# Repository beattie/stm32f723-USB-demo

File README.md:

# STM32F723 USB Passthrough Demo

A hardware and firmware demonstration platform based on the STM32F723VET6, a Cortex-M7
with an embedded USB HS PHY. Inspired by the [Pastilda](https://github.com/nickcoutsos/pastilda)
project, with a goal of providing robust Linux support for USB keyboard passthrough. This project was started as a vehicle to learn Rust and keep my USB up-to date as well as display my limited HW design abilities.

## Concept

The board sits between a USB keyboard and a Linux host. The firmware intercepts keystrokes,
allowing for key remapping, macros, and other HID transformations entirely in hardware —
no kernel modules or userspace daemons required on the host.

## Hardware

Designed in KiCad. The STM32F723 was chosen for its embedded USB HS PHY, which allows
full-speed USB HS without an external PHY chip.

**Key interfaces:**
- USB-C device port to host (USB 2.0 HS)
- USB-A host port for keyboard (USB FS)
- USB-C power input
- MicroSD — for config and macro storage
- SPI LCD connector — optional display
- SWD debug header

**Hardware versions:**
- Rev 0.1 — 2-layer board, initial bring-up (bring-up in progress)
- Rev 0.2 — 4-layer board (F.Cu / GND / 3V3 / B.Cu), revised layout (design in progress)

PCB gerbers for Rev 0.1 are in `kicad/gerbers/`.

## Firmware

Written in Rust using the [Embassy](https://embassy.dev/) async embedded framework.

```
src/main.rs      — application entry point
Cargo.toml       — dependencies
memory.x         — linker memory map for STM32F723VE
```

**Build:**
```bash
cargo build --release
```

Requires the `thumbv7em-none-eabihf` target:
```bash
rustup target add thumbv7em-none-eabihf
```

**Flash:**
```bash
cargo flash --release --chip STM32F723VETx
```
Or use OpenOCD/probe-rs via the SWD header.

## Bill of Materials

See [BOM.md](BOM.md) for the full parts list with Digikey part numbers.

## License

Hardware and firmware are released under CERN-OHL-S v2 / GPL v3 respectively.

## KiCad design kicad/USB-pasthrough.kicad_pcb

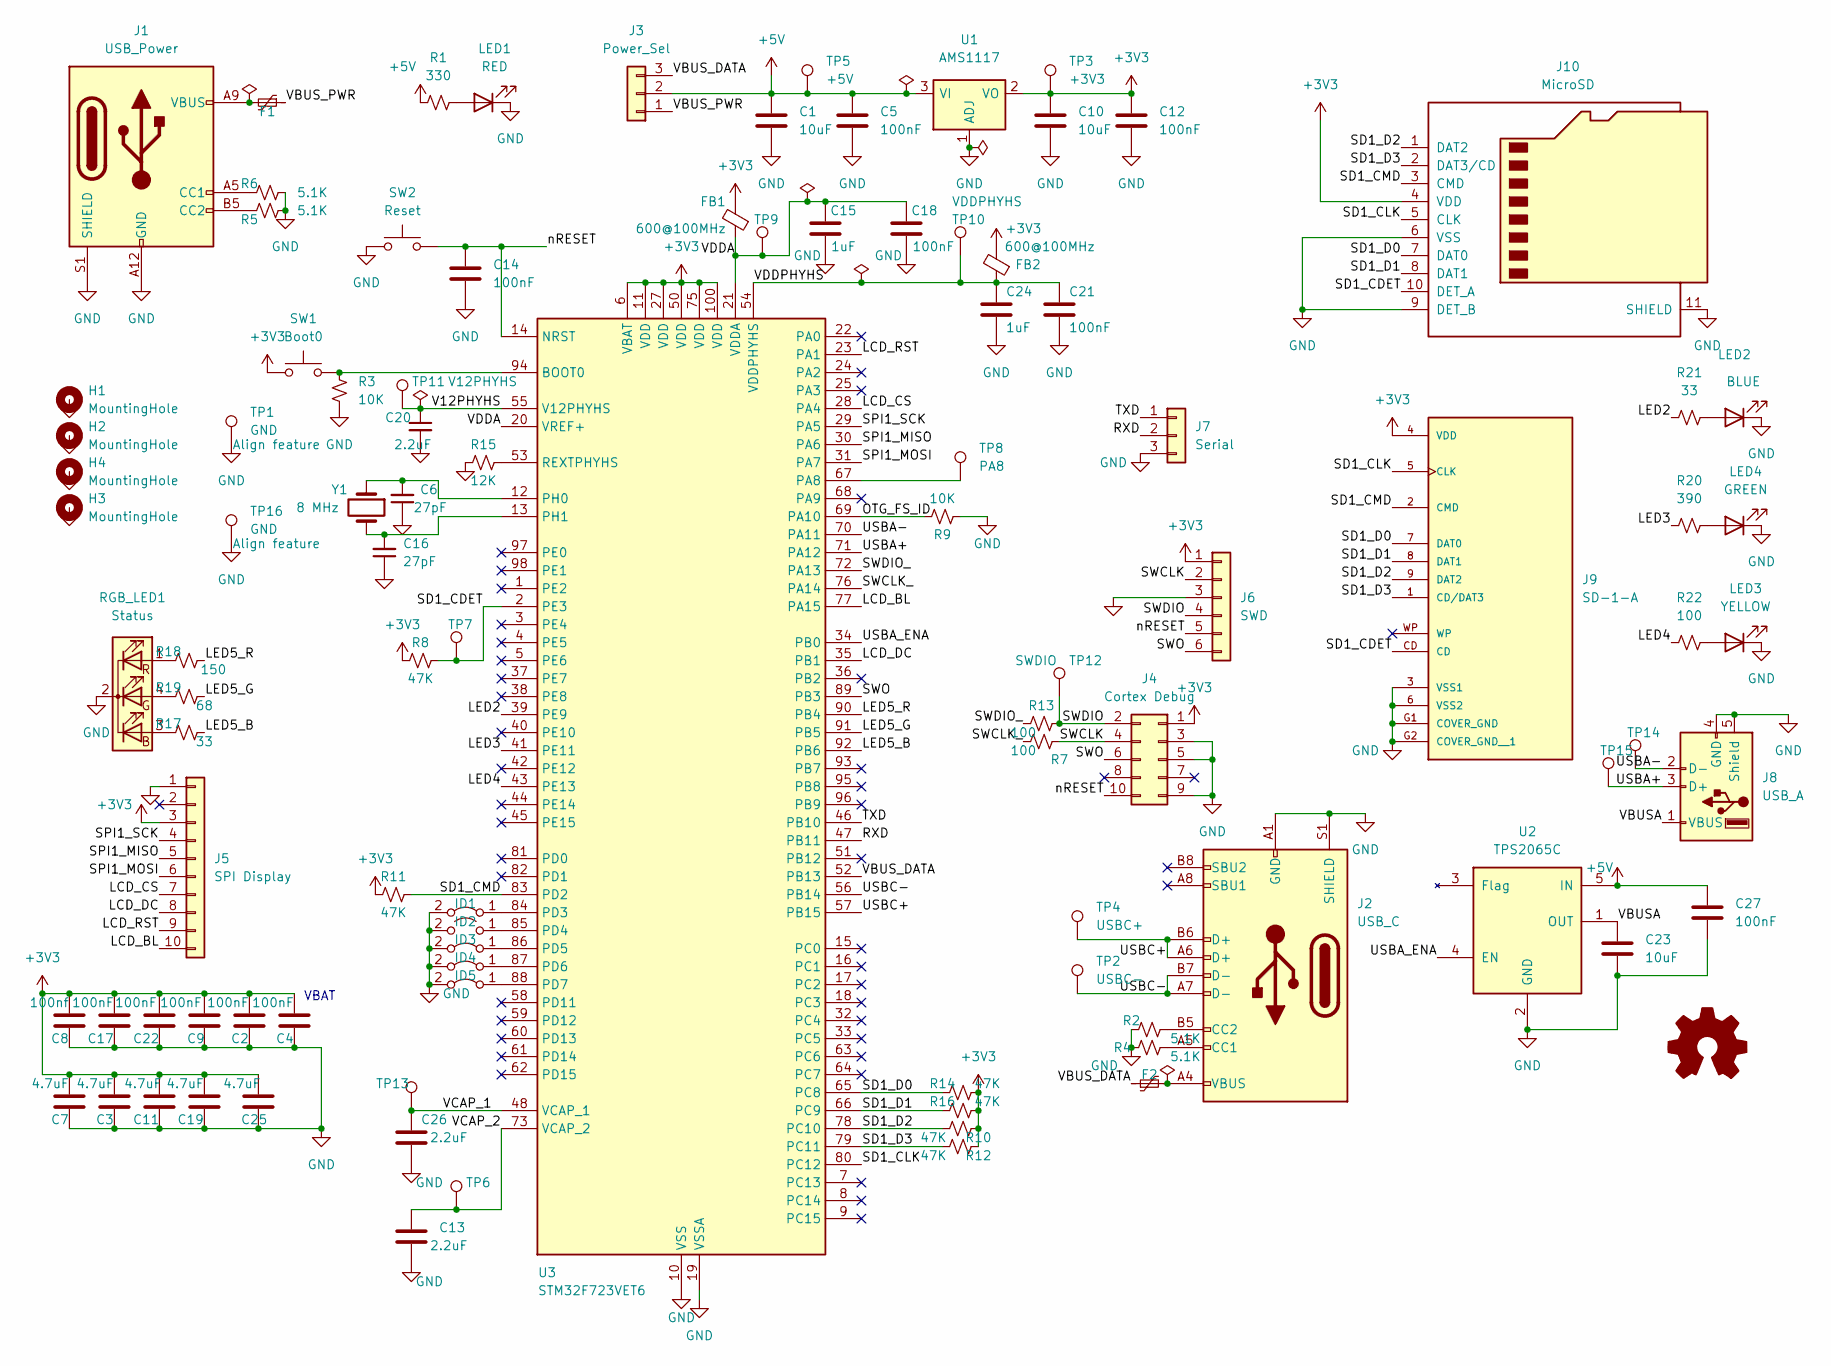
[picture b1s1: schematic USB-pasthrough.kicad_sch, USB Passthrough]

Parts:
C1, C10: 10uF; CP_Radial_D5.0mm_P2.50mm
C2, C4, C5, C9, C12, C14, C17, C18, C21, C22, C27: 100nF; C_0603_1608Metric_Pad1.08x0.95mm_HandSolder
C3, C7, C11, C19, C25: 4.7uF; C_0603_1608Metric_Pad1.08x0.95mm_HandSolder
C6, C16: 27pF; C_0603_1608Metric_Pad1.08x0.95mm_HandSolder
C8: 100nf; C_0603_1608Metric_Pad1.08x0.95mm_HandSolder
C13, C20, C26: 2.2uF; C_0603_1608Metric_Pad1.08x0.95mm_HandSolder
C15, C24: 1uF; C_0603_1608Metric_Pad1.08x0.95mm_HandSolder
C23: 10uF; C_0603_1608Metric_Pad1.08x0.95mm_HandSolder
F1, F2: F; Fuse_1812_4532Metric_Pad1.30x3.40mm_HandSolder
FB1, FB2: 600@100MHz; L_0603_1608Metric_Pad1.05x0.95mm_HandSolder
H1, H2, H3, H4: MountingHole; MountingHole_2.2mm_M2_Pad
ID1, ID3, ID4, ID5: Jumper_2_Bridged; SolderJumper-2_P1.3mm_Bridged_Pad1.0x1.5mm
ID2: Jumper_2_Bridged; SolderJumper-2_P1.3mm_Open_Pad1.0x1.5mm
J1: USB_Power; USB_C_Receptacle_GCT_USB4135-GF-A_6P_TopMnt_Horizontal
J2: USB_C; USB_C_Receptacle_GCT_USB4085
J3: Power_Sel; PinHeader_1x03_P2.54mm_Vertical
J4: Cortex Debug; SAMTEC_SHF-105-01-F-D-TH
J5: SPI Display; PinHeader_1x10_P2.54mm_Vertical
J6: SWD; PinHeader_1x06_P2.54mm_Vertical
J7: Serial; PinHeader_1x03_P2.54mm_Vertical
J8: USB_A; USB_A_Molex_67643_Horizontal
J9: SD-1-A; CUI_SD-1-A; PARTREV 1.0
J10: MicroSD; microSD_HC_Hirose_DM3AT-SF-PEJM5
LED1: RED; LED_0603_1608Metric_Pad1.05x0.95mm_HandSolder
LED2: BLUE; LED_0603_1608Metric_Pad1.05x0.95mm_HandSolder
LED3: YELLOW; LED_0603_1608Metric_Pad1.05x0.95mm_HandSolder
LED4: GREEN; LED_0603_1608Metric_Pad1.05x0.95mm_HandSolder
R1: 330; R_0603_1608Metric_Pad0.98x0.95mm_HandSolder
R2, R4, R5, R6: 5.1K; R_0603_1608Metric_Pad0.98x0.95mm_HandSolder
R3, R9: 10K; R_0603_1608Metric_Pad0.98x0.95mm_HandSolder
R7, R13, R22: 100; R_0603_1608Metric_Pad0.98x0.95mm_HandSolder
R8, R10, R11, R12, R14, R16: 47K; R_0603_1608Metric_Pad0.98x0.95mm_HandSolder
R15: 12K; R_0603_1608Metric_Pad0.98x0.95mm_HandSolder
R17, R21: 33; R_0603_1608Metric_Pad0.98x0.95mm_HandSolder
R18: 150; R_0603_1608Metric_Pad0.98x0.95mm_HandSolder
R19: 68; R_0603_1608Metric_Pad0.98x0.95mm_HandSolder
R20: 390; R_0603_1608Metric_Pad0.98x0.95mm_HandSolder
RGB_LED1: Status; LED_D5.0mm-4_RGB
SW1: Boot0; SW_Push_6mm_2pin_5.08mm
SW2: Reset; SW_Push_6mm_2pin_5.08mm
TP1, TP16: GND; TestPoint_THTPad_D2.0mm_Drill0.8mm_Align
TP2: USBC-; TestPoint_Pad_D1.0mm
TP3: +3V3; TestPoint_Pad_D1.0mm
TP4: USBC+; TestPoint_Pad_D1.0mm
TP5: +5V; TestPoint_Pad_D1.0mm
TP6: VCAP_2; TestPoint_Pad_D1.0mm
TP7: SD1_CDET; TestPoint_Pad_D1.0mm
TP8: PA8; TestPoint_Pad_D1.0mm
TP9: VDDA; TestPoint_Pad_D1.0mm
TP10: VDDPHYHS; TestPoint_Pad_D1.0mm
TP11: V12PHYHS; TestPoint_Pad_D1.0mm
TP12: SWDIO; TestPoint_Pad_D1.0mm
TP13: VCAP_1; TestPoint_Pad_D1.0mm
TP14: USBA-; TestPoint_Pad_D1.0mm
TP15: USBA+; TestPoint_Pad_D1.0mm
U1: AMS1117; SOT-223-3_TabPin2
U2: TPS2065C; SOT-23-5
U3: STM32F723VET6; LQFP-100_14x14mm_P0.5mm
Y1: 8 MHz; Crystal_HC49-U_Vertical

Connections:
+3V3: C2.2, C3.2, C4.2, C7.2, C8.2, C9.1, C10.1, C11.1, C12.1, C17.2, C19.2, C22.1, C25.1, FB1.2, FB2.2, J4.1, J5.3, J6.1, J9.4 (VDD), J10.4 (VDD), R8.1, R10.1, R11.1, R12.1, R14.2, R16.2, SW1.2, TP3.1, U1.2 (VO), U3.6 (VBAT), U3.11 (VDD), U3.27 (VDD), U3.50 (VDD), U3.75 (VDD), U3.100 (VDD)
+5V: C1.1, C5.2, C27.1, J3.2, R1.1, TP5.1, U1.3 (VI), U2.5 (IN)
/LCD_BL: J5.10, U3.77 (PA15)
/LCD_CS: J5.7, U3.28 (PA4)
/LCD_DC: J5.8, U3.35 (PB1)
/LCD_RST: J5.9, U3.23 (PA1)
/LED2: R21.1, U3.39 (PE9)
/LED3: R20.1, U3.41 (PE11)
/LED4: R22.1, U3.43 (PE13)
/LED5_B: R17.2, U3.92 (PB6)
/LED5_G: R19.2, U3.91 (PB5)
/LED5_R: R18.1, U3.90 (PB4)
/OTG_FS_ID: R9.2, U3.69 (PA10)
/RXD: J7.2, U3.25 (PA3), U3.47 (PB11)
/SD1_CDET: J9.CD, J10.10 (DET_A), R8.2, TP7.1, U3.2 (PE3)
/SD1_CLK: J9.5 (CLK), J10.5 (CLK), U3.80 (PC12)
/SD1_CMD: J9.2 (CMD), J10.3 (CMD), R11.2, U3.83 (PD2)
/SD1_D0: J9.7 (DAT0), J10.7 (DAT0), R14.1, U3.65 (PC8)
/SD1_D1: J9.8 (DAT1), J10.8 (DAT1), R16.1, U3.66 (PC9)
/SD1_D2: J9.9 (DAT2), J10.1 (DAT2), R10.2, U3.78 (PC10)
/SD1_D3: J9.1 (CD/DAT3), J10.2 (DAT3/CD), R12.2, U3.79 (PC11)
/SPI1_MISO: J5.5, U3.30 (PA6)
/SPI1_MOSI: J5.6, U3.31 (PA7)
/SPI1_SCK: J5.4, U3.29 (PA5)
/SWCLK: J4.4, J6.2, R7.2
/SWCLK_: R7.1, U3.76 (PA14)
/SWDIO: J4.2, J6.4, R13.2, TP12.1
/SWDIO_: R13.1, U3.72 (PA13)
/SWO: J4.6, J6.6, U3.89 (PB3)
/TXD: J7.1, U3.24 (PA2), U3.46 (PB10)
/USBA+: J8.3 (D+), TP15.1, U3.71 (PA12)
/USBA-: J8.2 (D-), TP14.1, U3.70 (PA11)
/USBA_ENA: U2.4 (EN), U3.34 (PB0)
/USBC+: J2.A6 (D+), J2.B6 (D+), TP4.1, U3.57 (PB15)
/USBC-: J2.A7 (D-), J2.B7 (D-), TP2.1, U3.56 (PB14)
/V12PHYHS: C20.1, TP11.1, U3.55 (V12PHYHS)
/VBUSA: C23.1, J8.1 (VBUS), U2.1 (OUT)
/VBUS_DATA: F2.1, J3.3, U3.52 (PB13)
/VBUS_PWR: F1.1, J3.1
/VCAP_1: C26.1, TP13.1, U3.48 (VCAP_1)
/VCAP_2: C13.1, TP6.1, U3.73 (VCAP_2)
/VDDA: C15.1, C18.1, FB1.1, TP9.1, U3.20 (VREF+), U3.21 (VDDA)
/VDDPHYHS: C21.1, C24.1, FB2.1, TP10.1, U3.54 (VDDPHYHS)
/nRESET: C14.1, J4.10, J6.5, SW2.1, U3.14 (NRST)
GND: C1.2, C2.1, C3.1, C4.1, C5.1, C6.1, C7.1, C8.1, C9.2, C10.2, C11.2, C12.2, C13.2, C14.2, C15.2, C16.1, C17.1, C18.2, C19.1, C20.2, C21.2, C22.2, C23.2, C24.2, C25.2, C26.2, C27.2, ID1.2 (B), ID2.2 (B), ID3.2 (B), ID4.2 (B), ID5.2 (B), J1.A12 (GND), J1.B12 (GND), J1.S1 (SHIELD), J2.A1 (GND), J2.A12 (GND), J2.B1 (GND), J2.B12 (GND), J2.S1 (SHIELD), J4.3, J4.5, J4.9, J5.1, J6.3, J7.3, J8.4 (GND), J8.5 (Shield), J9.3 (VSS1), J9.6 (VSS2), J9.G1 (COVER_GND), J9.G2 (COVER_GND__1), J10.6 (VSS), J10.9 (DET_B), J10.11 (SHIELD), LED1.1 (K), LED2.1 (K), LED3.1 (K), LED4.1 (K), R2.2, R3.2, R4.2, R5.2, R6.2, R9.1, R15.2, RGB_LED1.2 (K), SW2.2, TP1.1, TP16.1, U1.1 (ADJ), U2.2 (GND), U3.10 (VSS), U3.19 (VSSA), U3.26 (VSS), U3.49 (VSS), U3.74 (VSS), U3.99 (VSS)
unnamed: C6.2, U3.12 (PH0), Y1.1
unnamed: C16.2, U3.13 (PH1), Y1.2
unnamed: F1.2, J1.A9 (VBUS), J1.B9 (VBUS)
unnamed: F2.2, J2.A4 (VBUS), J2.A9 (VBUS), J2.B4 (VBUS), J2.B9 (VBUS)
unnamed: ID1.1 (A), U3.84 (PD3)
unnamed: ID2.1 (A), U3.85 (PD4)
unnamed: ID3.1 (A), U3.86 (PD5)
unnamed: ID4.1 (A), U3.87 (PD6)
unnamed: ID5.1 (A), U3.88 (PD7)
unnamed: J1.A5 (CC1), R6.1
unnamed: J1.B5 (CC2), R5.1
unnamed: J2.A5 (CC1), R4.1
unnamed: J2.B5 (CC2), R2.1
unnamed: LED1.2 (A), R1.2
unnamed: LED2.2 (A), R21.2
unnamed: LED4.2 (A), R20.2
unnamed: LED3.2 (A), R22.2
unnamed: R3.1, SW1.1, U3.94 (BOOT0)
unnamed: R15.1, U3.53 (REXTPHYHS)
unnamed: R17.1, RGB_LED1.3 (BA)
unnamed: R18.2, RGB_LED1.1 (RA)
unnamed: R19.1, RGB_LED1.4 (GA)
unnamed: TP8.1, U3.67 (PA8)

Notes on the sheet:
VBAT

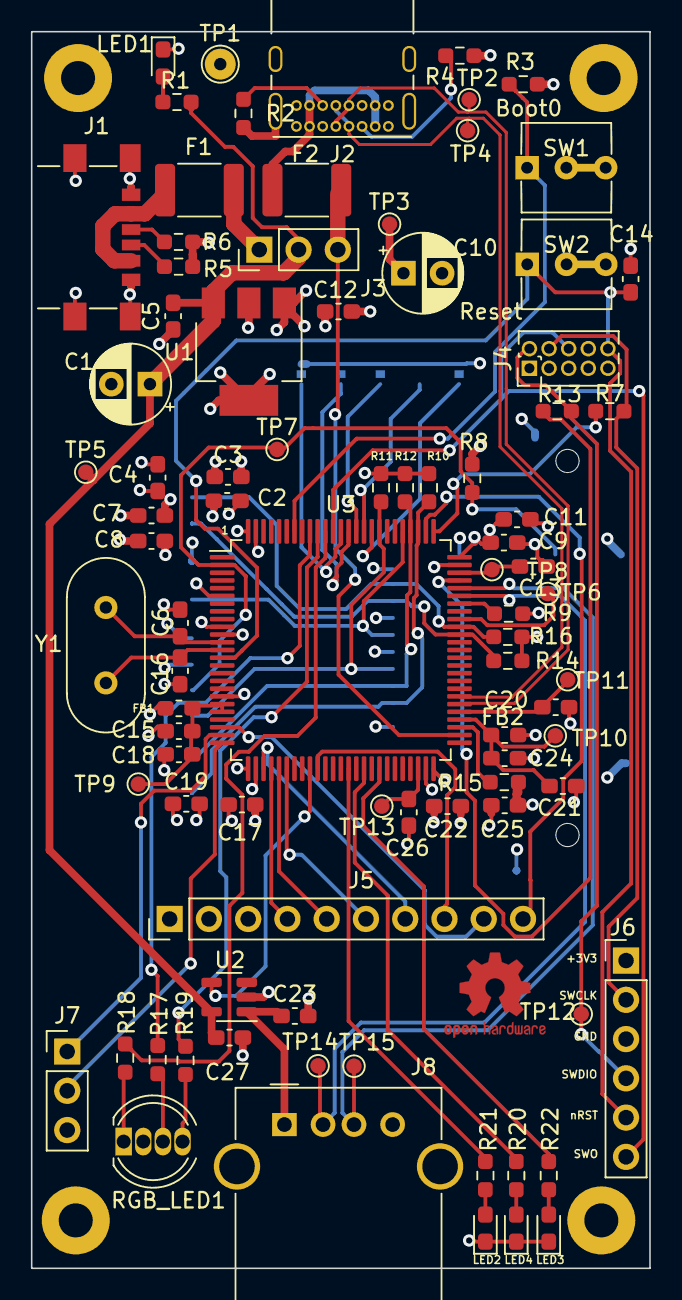
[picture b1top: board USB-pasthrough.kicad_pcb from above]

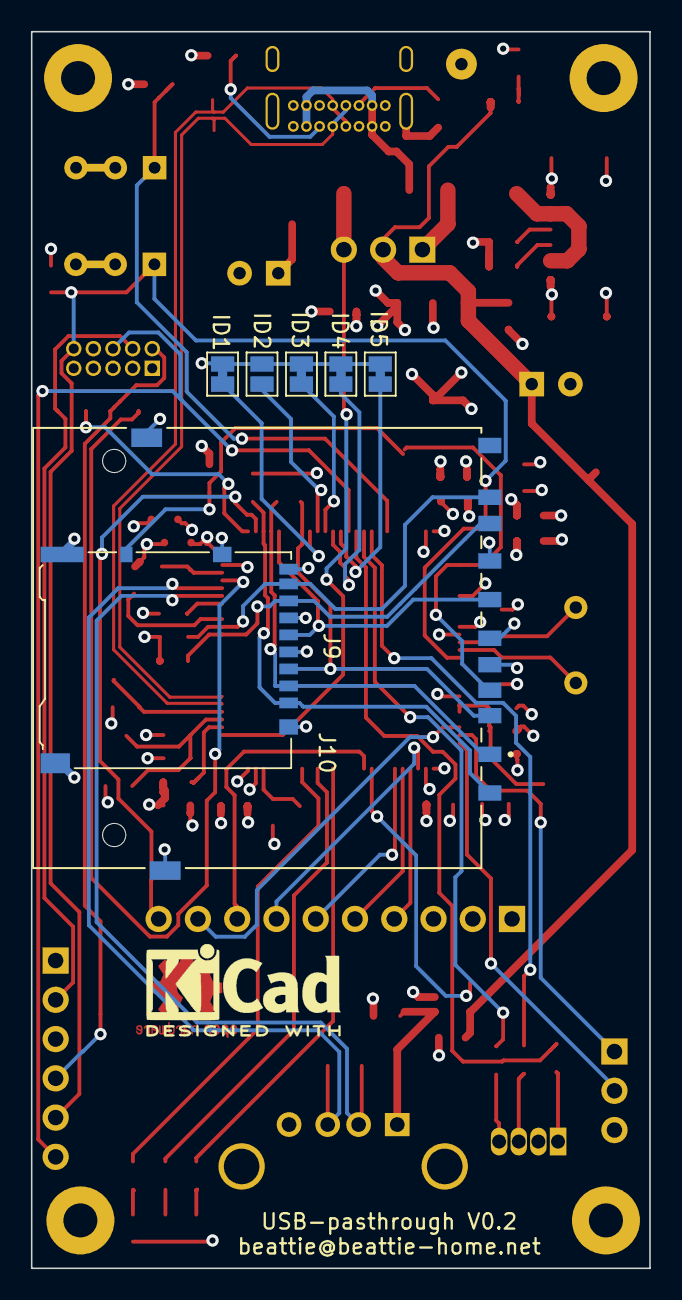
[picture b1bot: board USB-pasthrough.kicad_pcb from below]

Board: 4 copper layers, 40.0 x 80.0 mm, 98 parts (7 on the bottom side), 68 nets.

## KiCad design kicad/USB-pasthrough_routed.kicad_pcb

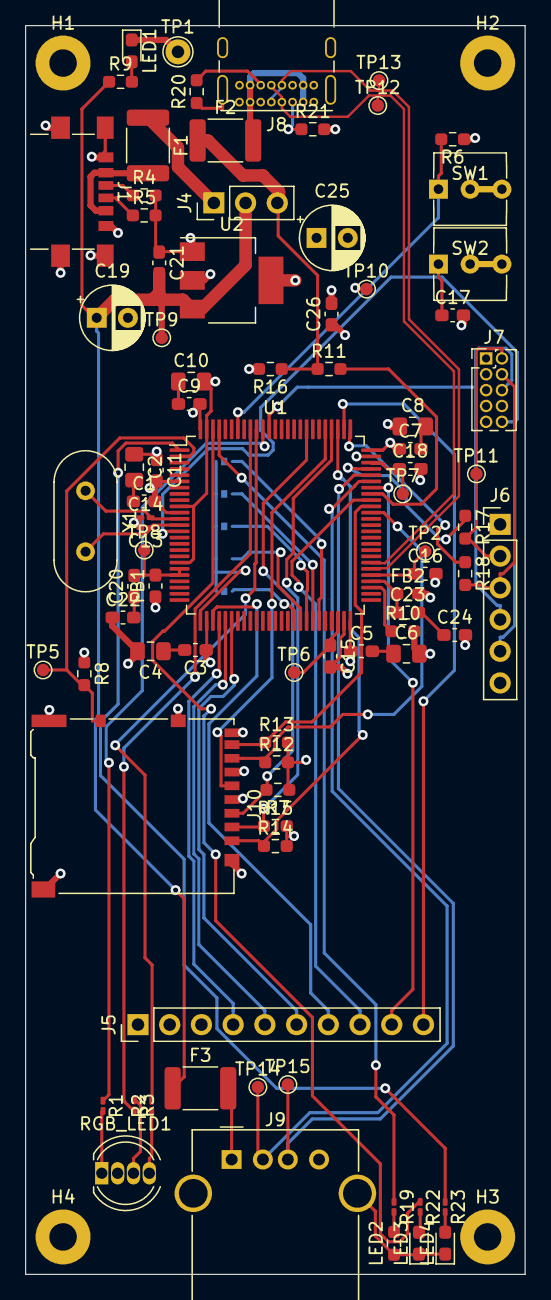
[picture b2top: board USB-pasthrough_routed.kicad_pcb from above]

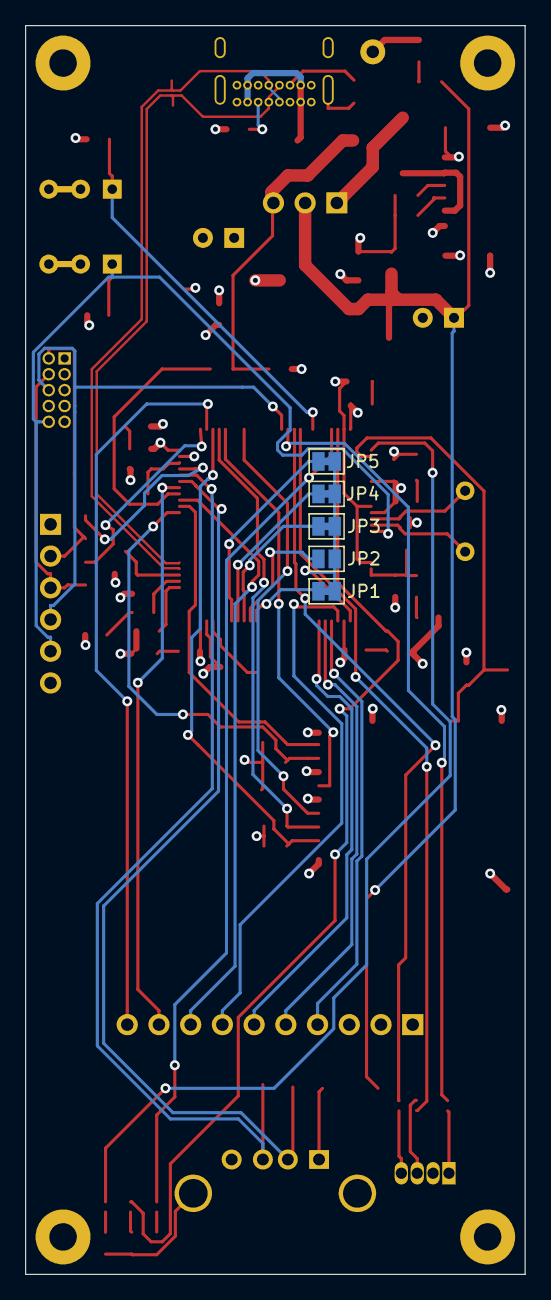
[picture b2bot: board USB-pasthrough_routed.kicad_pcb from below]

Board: 4 copper layers, 40.0 x 100.0 mm, 93 parts (5 on the bottom side), 71 nets.

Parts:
C1: 100nf; C_0603_1608Metric_Pad1.08x0.95mm_HandSolder
C2, C4, C6, C8, C10: 4.7uF; C_0805_2012Metric_Pad1.18x1.45mm_HandSolder
C3, C5, C7, C9, C11, C17, C21, C22, C24, C26: 100nF; C_0603_1608Metric_Pad1.08x0.95mm_HandSolder
C13, C14: 27pF; C_0201_0603Metric_Pad0.64x0.40mm_HandSolder
C15, C16, C18: 2.2uF; C_0603_1608Metric_Pad1.08x0.95mm_HandSolder
C19, C25: 10uF; CP_Radial_D5.0mm_P2.50mm
C20, C23: 1uF; C_0603_1608Metric_Pad1.08x0.95mm_HandSolder
F1, F2, F3: F; Fuse_1812_4532Metric_Pad1.30x3.40mm_HandSolder
FB1, FB2: 600@100MHz; L_0603_1608Metric_Pad1.05x0.95mm_HandSolder
H1, H2, H3, H4: MountingHole; MountingHole_2.2mm_M2_Pad
J1: USB_Power; USB_C_Receptacle_GCT_USB4135-GF-A_6P_TopMnt_Horizontal
J4: Power_Sel; PinHeader_1x03_P2.54mm_Vertical
J5: SPI Display; PinHeader_1x10_P2.54mm_Vertical
J6: SWD; PinHeader_1x06_P2.54mm_Vertical
J7: Cortex Debug; PinHeader_2x05_P1.27mm_Vertical
J8: USB_C; USB_C_Receptacle_GCT_USB4085
J9: USB_A; USB_A_Molex_67643_Horizontal
J10: MicroSD; microSD_HC_Hirose_DM3AT-SF-PEJM5
JP1: ID0; SolderJumper-2_P1.3mm_Bridged_Pad1.0x1.5mm
JP2: ID1; SolderJumper-2_P1.3mm_Open_Pad1.0x1.5mm
JP3: ID2; SolderJumper-2_P1.3mm_Bridged_Pad1.0x1.5mm
JP4: ID3; SolderJumper-2_P1.3mm_Bridged_Pad1.0x1.5mm
JP5: ID4; SolderJumper-2_P1.3mm_Bridged_Pad1.0x1.5mm
LED1: RED; LED_0603_1608Metric_Pad1.05x0.95mm_HandSolder
LED2: BLUE; R_0603_1608Metric_Pad0.98x0.95mm_HandSolder
LED3: GREEN; LED_0603_1608Metric_Pad1.05x0.95mm_HandSolder
LED4: YELLOW; LED_0603_1608Metric_Pad1.05x0.95mm_HandSolder
R1, R23: 150; R_0201_0603Metric_Pad0.64x0.40mm_HandSolder
R2, R22: 68; R_0201_0603Metric_Pad0.64x0.40mm_HandSolder
R3, R19: 33; R_0201_0603Metric_Pad0.64x0.40mm_HandSolder
R4, R5, R20, R21: 5.1K; R_0603_1608Metric_Pad0.98x0.95mm_HandSolder
R6: 10K; R_0603_1608Metric_Pad0.98x0.95mm_HandSolder
R7, R8, R12, R13, R14, R15: 47K; R_0603_1608Metric_Pad0.98x0.95mm_HandSolder
R9: 330; R_0603_1608Metric_Pad0.98x0.95mm_HandSolder
R10: 12K; R_0603_1608Metric_Pad0.98x0.95mm_HandSolder
R11: 100K; R_0603_1608Metric_Pad0.98x0.95mm_HandSolder
R16: 220k; R_0603_1608Metric_Pad0.98x0.95mm_HandSolder
R17, R18: 100; R_0603_1608Metric_Pad0.98x0.95mm_HandSolder
RGB_LED1: Status; LED_D5.0mm-4_RGB
SW1: Boot0; SW_Push_6mm_2pin_5.08mm
SW2: Reset; SW_Push_6mm_2pin_5.08mm
TP1: GND; TestPoint_THTPad_D2.0mm_Drill1.0mm
TP2: V12PHYHS; TestPoint_Pad_D1.0mm
TP5: MMC1_CDET; TestPoint_Pad_D1.0mm
TP6: VCAP_1; TestPoint_Pad_D1.0mm
TP7: VCAP_2; TestPoint_Pad_D1.0mm
TP8: VDDA; TestPoint_Pad_D1.0mm
TP9: +5V; TestPoint_Pad_D1.0mm
TP10: +3V3; TestPoint_Pad_D1.0mm
TP11: SWDIO; TestPoint_Pad_D1.0mm
TP12: USBC+; TestPoint_Pad_D1.0mm
TP13: USBC-; TestPoint_Pad_D1.0mm
TP14: USBA-; TestPoint_Pad_D1.0mm
TP15: USBA+; TestPoint_Pad_D1.0mm
U1: STM32F723VET6; LQFP-100_14x14mm_P0.5mm
U2: AMS1117; SOT-223-3_TabPin2
Y1: 8 MHz; Crystal_HC49-U_Vertical

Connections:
+3V3: C1.2, C3.1, C5.1, C7.1, C9.2, C11.2, C25.1, C26.2, FB1.1, FB2.2, J5.3, J6.1, J7.1, J10.4 (VDD), R7.1, R8.1, R12.2, R13.2, R14.2, R15.2, SW1.2, TP10.1, U1.6 (VBAT), U1.11 (VDD), U1.27 (VDD), U1.50 (VDD), U1.75 (VDD), U1.100 (VDD), U2.2 (VO)
+5V: C19.1, C21.2, F3.1, J4.2, R9.1, TP9.1, U2.3 (VI)
/ID0: JP1.1 (A), U1.41 (PE11)
/ID1: JP2.1 (A), U1.42 (PE12)
/ID2: JP3.1 (A), U1.43 (PE13)
/ID3: JP4.1 (A), U1.44 (PE14)
/ID4: JP5.1 (A), U1.45 (PE15)
/LCD_BL: J5.10, U1.77 (PA15)
/LCD_CS: J5.7, U1.28 (PA4)
/LCD_DC: J5.8, U1.67 (PA8)
/LCD_RST: J5.9, U1.69 (PA10)
/LED2: R19.1, U1.97 (PE0)
/LED3: R22.1, U1.98 (PE1)
/LED4: R23.1, U1.1 (PE2)
/LED5_B: R3.2, U1.92 (PB6)
/LED5_G: R2.2, U1.91 (PB5)
/LED5_R: R1.1, U1.90 (PB4)
/MMC1_CDET: J10.10 (DET_A), R8.2, TP5.1, U1.2 (PE3)
/MMC1_CLK: J10.5 (CLK), U1.80 (PC12)
/MMC1_CMD: J10.3 (CMD), R7.2, U1.83 (PD2)
/MMC1_D0: J10.7 (DAT0), R12.1, U1.65 (PC8)
/MMC1_D1: J10.8 (DAT1), R13.1, U1.66 (PC9)
/MMC1_D2: J10.1 (DAT2), R14.1, U1.78 (PC10)
/MMC1_D3: J10.2 (DAT3/CD), R15.1, U1.79 (PC11)
/PA13: R17.1, U1.72 (PA13)
/PA14: R18.1, U1.76 (PA14)
/SPI1_MISO: J5.5, U1.30 (PA6)
/SPI1_MOSI: J5.6, U1.31 (PA7)
/SPI1_SCK: J5.4, U1.29 (PA5)
/SWCLK: J6.3, J7.4, R18.2
/SWDIO: J6.2, J7.2, R17.2, TP11.1
/SWO: J6.4, J7.6, U1.89 (PB3)
/USBA+: J9.3 (D+), TP15.1, U1.71 (PA12)
/USBA-: J9.2 (D-), TP14.1, U1.70 (PA11)
/USBC+: J8.A6 (D+), J8.B6 (D+), TP12.1, U1.57 (PB15)
/USBC-: J8.A7 (D-), J8.B7 (D-), TP13.1, U1.56 (PB14)
/V12PHYHS: C16.1, TP2.1, U1.55 (V12PHYHS)
/VBUS_DATA: F2.1, J4.3, R11.1, R16.1
/VBUS_PWR: F1.1, J4.1
/VCAP_1: C15.1, TP6.1, U1.48 (VCAP_1)
/VCAP_2: C18.1, TP7.1, U1.73 (VCAP_2)
/VDDA: C20.2, FB1.2, TP8.1, U1.20 (VREF+), U1.21 (VDDA)
/nRESET: C17.1, J6.5, J7.10, SW2.1, U1.14 (NRST)
GND: C2.1, C4.2, C6.2, C8.1, C10.2, C11.1, C13.2, C14.1, C15.2, C16.2, C17.2, C18.2, C19.2, C21.1, C22.1, C24.2, C25.2, C26.1, J1.A12 (GND), J1.B12 (GND), J1.S1 (SHIELD), J5.1, J6.6, J7.3, J7.5, J7.9, J8.A1 (GND), J8.A12 (GND), J8.B1 (GND), J8.B12 (GND), J8.S1 (SHIELD), J9.4 (GND), J9.5 (Shield), J10.6 (VSS), J10.9 (DET_B), J10.11 (SHIELD), JP1.2 (B), JP2.2 (B), JP3.2 (B), JP4.2 (B), JP5.2 (B), LED1.1 (K), LED2.1 (K), LED3.1 (K), LED4.1 (K), R4.2, R5.2, R6.1, R10.2, R16.2, R20.1, R21.2, RGB_LED1.2 (K), SW2.2, TP1.1, U1.10 (VSS), U1.19 (VSSA), U1.26 (VSS), U1.49 (VSS), U1.74 (VSS), U1.99 (VSS), U2.1 (ADJ)
unnamed: C1.1, C2.2
unnamed: C3.2, C4.1
unnamed: C5.2, C6.1
unnamed: C7.2, C8.2
unnamed: C9.1, C10.1
unnamed: C13.1, U1.13 (PH1), Y1.2
unnamed: C14.2, U1.12 (PH0), Y1.1
unnamed: C20.1, C22.2
unnamed: C23.1, FB2.1, U1.54 (VDDPHYHS)
unnamed: C23.2, C24.1
unnamed: F1.2, J1.A9 (VBUS), J1.B9 (VBUS)
unnamed: F2.2, J8.A4 (VBUS), J8.A9 (VBUS), J8.B4 (VBUS), J8.B9 (VBUS)
unnamed: F3.2, J9.1 (VBUS)
unnamed: J1.A5 (CC1), R4.1
unnamed: J1.B5 (CC2), R5.1
unnamed: J8.A5 (CC1), R21.1
unnamed: J8.B5 (CC2), R20.2
unnamed: LED1.2 (A), R9.2
unnamed: LED2.2 (A), R19.2
unnamed: LED3.2 (A), R22.2
unnamed: LED4.2 (A), R23.2
unnamed: R1.2, RGB_LED1.1 (RA)
unnamed: R2.1, RGB_LED1.4 (GA)
unnamed: R3.1, RGB_LED1.3 (BA)
unnamed: R6.2, SW1.1, U1.94 (BOOT0)
unnamed: R10.1, U1.53 (REXTPHYHS)
unnamed: R11.2, U1.68 (PA9)

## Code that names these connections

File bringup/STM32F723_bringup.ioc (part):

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Mcu.Name=STM32F723V(C-E)Tx
Mcu.Package=LQFP100
Mcu.UserName=STM32F723VETx
PA11.Mode=Host_Only
PA11.Signal=USB_OTG_FS_DM
PA12.Mode=Host_Only
PA12.Signal=USB_OTG_FS_DP
PA13.Signal=SYS_JTMS-SWDIO
PA14.Signal=SYS_JTCK-SWCLK
PA5.Mode=Full_Duplex_Master
PA5.Signal=SPI1_SCK
PA6.Mode=Full_Duplex_Master
PA6.Signal=SPI1_MISO
PA7.Mode=Full_Duplex_Master
PA7.Signal=SPI1_MOSI
PB14.Mode=Internal_Phy_Device
PB14.Signal=USB_OTG_HS_DM
PB15.Mode=Internal_Phy_Device
PB15.Signal=USB_OTG_HS_DP
PB3.Signal=SYS_JTDO-SWO
PB8.Mode=mmc_8_bits_Wide_bus
PB8.Signal=SDMMC1_D4
PB9.Mode=mmc_8_bits_Wide_bus
PB9.Signal=SDMMC1_D5
PC10.Mode=mmc_8_bits_Wide_bus
PC10.Signal=SDMMC1_D2
PC11.Mode=mmc_8_bits_Wide_bus
PC11.Signal=SDMMC1_D3
PC12.Mode=mmc_8_bits_Wide_bus
PC12.Signal=SDMMC1_CK
PC6.Mode=mmc_8_bits_Wide_bus
PC6.Signal=SDMMC1_D6
PC7.Mode=mmc_8_bits_Wide_bus
PC7.Signal=SDMMC1_D7
PC8.Mode=mmc_8_bits_Wide_bus
PC8.Signal=SDMMC1_D0
PC9.Mode=mmc_8_bits_Wide_bus
PC9.Signal=SDMMC1_D1
PD2.Mode=mmc_8_bits_Wide_bus
PD2.Signal=SDMMC1_CMD
PE0.Signal=GPIO_Output
PE1.Signal=GPIO_Output
PE11.Signal=GPIO_Input
PE12.Signal=GPIO_Input
PE13.Signal=GPIO_Input
PE14.Signal=GPIO_Input
PE15.Signal=GPIO_Input
PE2.Signal=GPIO_Output
PE3.Signal=GPIO_Input
PH0-OSC_IN.Mode=HSE-External-Oscillator
PH0-OSC_IN.Signal=RCC_OSC_IN
PH1-OSC_OUT.Mode=HSE-External-Oscillator
PH1-OSC_OUT.Signal=RCC_OSC_OUT
RCC.HSE_VALUE=12000000
RCC.SYSCLKFreq_VALUE=192000000
RCC.SYSCLKSource=RCC_SYSCLKSOURCE_PLLCLK
board=custom

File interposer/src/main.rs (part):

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    let p = embassy_stm32::init(config);

    // All LEDs off at init (active high; RGB red has enough leakage to glow if floating)
    let _rgb_r = Output::new(p.PB4,  Level::Low , GpioSpeed::Low); // RGB RED
    let _rgb_g = Output::new(p.PB5,  Level::Low , GpioSpeed::Low); // RGB GREEN
    let _rgb_b = Output::new(p.PB6,  Level::Low , GpioSpeed::Low); // RGB BLUE

    info!("STM32F723 Embassy bringup — SYSCLK=216MHz");

    let version = hw_version(p.PD4, p.PD5, p.PD6, p.PD7) + 1;
    HW_VERSION.store(version, Ordering::Relaxed);
    info!("Interposer version: {}", version);

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    info!("creating USB driver");
    let driver = UsbDriver::new_hs(
        p.USB_OTG_HS, Irqs,
        p.PB15, p.PB14, // DP, DM
        EP_OUT_BUF.init([0u8; 1024]),
        usb_config,
    );
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    let usb_device = builder.build();

    let _dm = {
        let mut pin = Flex::new(p.PA11);
        pin.set_as_af_unchecked(10, AfType::output(OutputType::PushPull,
                                                   GpioSpeed::VeryHigh));
        pin
    };

    let _dp = {
        let mut pin = Flex::new(p.PA12);
        pin.set_as_af_unchecked(10, AfType::output(OutputType::PushPull,
                                                   GpioSpeed::VeryHigh));
        pin
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    pac::RCC.apb2enr().modify(|w| w.set_usbphycen(true));
    unsafe { init_otgphyc(); }
    info!("spawning tasks");
    spawner.spawn(cdet_task(p.PE3).unwrap());
    info!("cdet spawned");
    spawner.spawn(usb_task(usb_device).unwrap());
    info!("usb spawned");

    spawner.spawn(led_task(p.PE9, p.PE11, p.PE13).unwrap());
    info!("led spawned");
    spawner.spawn(display_task(p.SPI1, p.PA5, p.PA7, p.PA4, p.PB1, p.PA1,
                               p.PA15).unwrap());
    info!("display spawned");
    spawner.spawn(kbd_task(controller, handle, p.PB0, hid_writer).unwrap());
    info!("keyboard spawned");

    let msc = MSC.init(msc);
    spawner.spawn(msc_task(msc,
            p.SDMMC1, p.DMA2_CH3,
            p.PC12, p.PD2,
            p.PC8, p.PC9, p.PC10, p.PC11,
                           ).unwrap());
    info!("msc spawned");

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}

fn hw_version(
    pd4: Peri<'static, embassy_stm32::peripherals::PD4>,
    pd5: Peri<'static, embassy_stm32::peripherals::PD5>,
    pd6: Peri<'static, embassy_stm32::peripherals::PD6>,
    pd7: Peri<'static, embassy_stm32::peripherals::PD7>,
) -> u8 {
    Input::new(pd4, Pull::Up).is_high() as u8 |
       ((Input::new(pd5, Pull::Up).is_high() as u8) << 1) |
       ((Input::new(pd6, Pull::Up).is_high() as u8) << 2) |
       ((Input::new(pd7, Pull::Up).is_high() as u8) << 3)
}
    

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async fn kbd_task(
    mut controller: BusController<'static, OtgHost<'static, 8>>,
    handle: BusHandle<'static, OtgHostAllocator<'static, 8>>,
    vbus_ena: Peri<'static, embassy_stm32::peripherals::PB0>,
    mut hid: HidWriter<'static, HsDriver, 8>,
) {
    // Enable USB-A VBUS
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
#[embassy_executor::task]
async fn led_task (
    pin_b: Peri<'static, embassy_stm32::peripherals::PE9>,
    pin_g: Peri<'static, embassy_stm32::peripherals::PE11>,
    pin_y: Peri<'static, embassy_stm32::peripherals::PE13>,
) {
    let _led_b     = Output::new(pin_b,  Level::High, GpioSpeed::Low); // BLUE
    let _led_g     = Output::new(pin_g, Level::Low , GpioSpeed::Low); // GREEN
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async fn sd_task(
    sdmmc:  Peri<'static, embassy_stm32::peripherals::SDMMC1>,
    dma:    Peri<'static, embassy_stm32::peripherals::DMA2_CH3>,
    clk:    Peri<'static, embassy_stm32::peripherals::PC12>,
    cmd:    Peri<'static, embassy_stm32::peripherals::PD2>,
    d0:     Peri<'static, embassy_stm32::peripherals::PC8>,
    _d1:     Peri<'static, embassy_stm32::peripherals::PC9>,
    _d2:     Peri<'static, embassy_stm32::peripherals::PC10>,
    _d3:     Peri<'static, embassy_stm32::peripherals::PC11>,
) {
    info!("SD task started");
    let mut buf: String<26> = String::new();
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#[embassy_executor::task]
async fn display_task(
    spi1: Peri<'static, embassy_stm32::peripherals::SPI1>,
    pa5:  Peri<'static, embassy_stm32::peripherals::PA5>,   // SCK
    pa7:  Peri<'static, embassy_stm32::peripherals::PA7>,   // MOSI
    pa4:  Peri<'static, embassy_stm32::peripherals::PA4>,   // CS
    pb1:  Peri<'static, embassy_stm32::peripherals::PB1>,   // DC
    pa1:  Peri<'static, embassy_stm32::peripherals::PA1>,   // RST
    pa15: Peri<'static, embassy_stm32::peripherals::PA15>,  // backlight
) {
    info!("Display Task started");
    let mut spi_config = embassy_stm32::spi::Config::default();
    spi_config.frequency = Hertz(12_000_000);
    let spi = embassy_stm32::spi::Spi::new_blocking_txonly(spi1, pa5, pa7,
                                                           spi_config);
    let dc  = Output::new(pb1, Level::High, GpioSpeed::Low);
    let rst = Output::new(pa1, Level::Low,  GpioSpeed::Low);
    let cs  = Output::new(pa4, Level::High, GpioSpeed::High);
    let _bl = Output::new(pa15,Level::High, GpioSpeed::Low);
    let spi_dev = embedded_hal_bus::spi::ExclusiveDevice::
                new_no_delay(spi, cs).unwrap();

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    msc: &'static mut msc::Msc<'static, HsDriver>,
    sdmmc:  Peri<'static, embassy_stm32::peripherals::SDMMC1>,
    dma:    Peri<'static, embassy_stm32::peripherals::DMA2_CH3>,
    clk:    Peri<'static, embassy_stm32::peripherals::PC12>,
    cmd:    Peri<'static, embassy_stm32::peripherals::PD2>,
    d0:     Peri<'static, embassy_stm32::peripherals::PC8>,
    _d1:    Peri<'static, embassy_stm32::peripherals::PC9>,
    _d2:    Peri<'static, embassy_stm32::peripherals::PC10>,
    _d3:    Peri<'static, embassy_stm32::peripherals::PC11>,
) {
    info!("MSC task started");
    let mut sd_hw = Sdmmc::new_1bit(sdmmc, dma, Irqs, clk, cmd, d0,
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}

#[embassy_executor::task]
async fn cdet_task(cdet: Peri<'static, embassy_stm32::peripherals::PE3>) {
    let pin = Input::new(cdet, Pull::None);
    loop {
        CARD_PRESENT.store(pin.is_low(), Ordering::Relaxed);
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
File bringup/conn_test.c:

/*
 * conn_test.c — GPIO connectivity test for STM32F723 custom board v0.1
 *
 * Standalone firmware (has its own main, replaces bringup for testing).
 * Build with: make flash_test
 *
 * All USB data lines, MMC data/clock/cmd, and SPI1_SCK are driven as plain
 * GPIO outputs with distinct toggle rates.  Probe each pin on the PCB or
 * connector with a scope to verify traces and solder joints.
 *
 * Outputs (all GPIO, no alternate function):
 *   PA5  SPI1_SCK  pin 29  ~1 Hz  — 1PPS reference; jump to PA10 for input test
 *   PA11 USBA_DM   pin 70  ~8 Hz
 *   PA12 USBA_DP   pin 71  ~16 Hz
 *   PB14 USBC_DM   pin 56  ~32 Hz
 *   PB15 USBC_DP   pin 57  ~64 Hz
 *   PC8  MMC_D0    pin 65  ~128 Hz
 *   PC9  MMC_D1    pin 66  ~256 Hz
 *   PC10 MMC_D2    pin 77  ~512 Hz
 *   PC11 MMC_D3    pin 78  ~1 kHz
 *   PC12 MMC_CLK   pin 79  ~2 kHz
 *   PD2  MMC_CMD   pin 82  ~4 kHz
 *
 * Input:
 *   PA10 LCD_RST / OTG_FS_ID  pin 69 — input with pull-down
 *   Jump PA5 → PA10 to verify input path.
 *   LED3 (PE1 GREEN)  lights while PA10 is high.
 *   LED4 (PE2 YELLOW) mirrors PA5 (~1 Hz heartbeat).
 *
 * Frequencies are approximate; they scale with CPU speed.
 * At HSI16 (16 MHz) with -O0 the counter runs at ~100–150 k iter/s,
 * so bit 17 ≈ 1 Hz, each lower bit doubles the frequency.
 */

#include <stdint.h>

/* ---- RCC ---- */
#define RCC_AHB1ENR  (*(volatile uint32_t *)0x40023830UL)

/* ---- GPIO helpers ---- */
/* Port indices: A=0, B=1, C=2, D=3, E=4 */
#define GPIO_BASE(p)   (0x40020000UL + (uint32_t)(p) * 0x400UL)
#define MODER(p)       (*(volatile uint32_t *)(GPIO_BASE(p) + 0x00))
#define OSPEEDR(p)     (*(volatile uint32_t *)(GPIO_BASE(p) + 0x08))
#define PUPDR(p)       (*(volatile uint32_t *)(GPIO_BASE(p) + 0x0C))
#define IDR(p)         (*(volatile uint32_t *)(GPIO_BASE(p) + 0x10))
#define BSRR(p)        (*(volatile uint32_t *)(GPIO_BASE(p) + 0x18))

#define PA 0
#define PB 1
#define PC 2
#define PD 3
#define PE 4

/* Atomic set (val=1) or reset (val=0) of a single pin via BSRR */
static inline void pin_out(int port, int pin, uint32_t val)
{
    if (val) BSRR(port) = (1u << pin);
    else     BSRR(port) = (1u << (pin + 16));
}

/* Configure a pin as push-pull output, very-high-speed */
static void cfg_out(int port, int pin)
{
    MODER(port)   = (MODER(port)   & ~(3u << (pin * 2))) | (1u << (pin * 2));
    OSPEEDR(port) = (OSPEEDR(port) | (3u << (pin * 2)));
}

/* Configure a pin as floating input with pull-down */
static void cfg_in_pd(int port, int pin)
{
    MODER(port) &= ~(3u << (pin * 2));                                 /* input */
    PUPDR(port)  = (PUPDR(port) & ~(3u << (pin * 2))) | (2u << (pin * 2)); /* pull-down */
}

int main(void)
{
    /* Enable GPIOA–E clocks */
    RCC_AHB1ENR |= (1u<<0)|(1u<<1)|(1u<<2)|(1u<<3)|(1u<<4);

    /* Output pins */
    cfg_out(PA,  5);   /* SPI1_SCK  — 1PPS reference */
    cfg_out(PA, 11);   /* USBA_DM  */
    cfg_out(PA, 12);   /* USBA_DP  */
    cfg_out(PB, 14);   /* USBC_DM  */
    cfg_out(PB, 15);   /* USBC_DP  */
    cfg_out(PC,  8);   /* MMC_D0   */
    cfg_out(PC,  9);   /* MMC_D1   */
    cfg_out(PC, 10);   /* MMC_D2   */
    cfg_out(PC, 11);   /* MMC_D3   */
    cfg_out(PC, 12);   /* MMC_CLK  */
    cfg_out(PD,  2);   /* MMC_CMD  */
    cfg_out(PE,  1);   /* LED3 (GREEN)  */
    cfg_out(PE,  2);   /* LED4 (YELLOW) */

    /* Input pin: PA10 (LCD_RST / OTG_FS_ID) — jumper to PA5 to test */
    cfg_in_pd(PA, 10);

    uint32_t c = 0;
    while (1) {
        c++;

        /*
         * Each output is driven by one bit of the counter.
         * Bit N gives a square wave with period = 2^(N+1) iterations.
         * At ~120 k iter/s (HSI16, -O0):
         *   bit 17 ≈ 1 Hz, bit 14 ≈ 8 Hz, …, bit 5 ≈ 4 kHz
         */
        pin_out(PA,  5, (c >> 17) & 1);   /* ~1 Hz  — 1PPS */
        pin_out(PA, 11, (c >> 14) & 1);   /* ~8 Hz  */
        pin_out(PA, 12, (c >> 13) & 1);   /* ~16 Hz */
        pin_out(PB, 14, (c >> 12) & 1);   /* ~32 Hz */
        pin_out(PB, 15, (c >> 11) & 1);   /* ~64 Hz */
        pin_out(PC,  8, (c >> 10) & 1);   /* ~128 Hz */
        pin_out(PC,  9, (c >>  9) & 1);   /* ~256 Hz */
        pin_out(PC, 10, (c >>  8) & 1);   /* ~512 Hz */
        pin_out(PC, 11, (c >>  7) & 1);   /* ~1 kHz */
        pin_out(PC, 12, (c >>  6) & 1);   /* ~2 kHz */
        pin_out(PD,  2, (c >>  5) & 1);   /* ~4 kHz */

        /* LED3: lit while PA10 is high (jumpered to PA5) */
        pin_out(PE, 1, (IDR(PA) >> 10) & 1);

        /* LED4: mirrors PA5 — visible heartbeat */
        pin_out(PE, 2, (c >> 17) & 1);
    }
    return 0;
}

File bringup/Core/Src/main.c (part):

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
UART_HandleTypeDef huart2;

/* v0.2 LED chase: PE9=BLUE, PE11=GREEN, PE13=YELLOW, PB4=RGB_R, PB5=RGB_G, PB6=RGB_B */
static const struct { GPIO_TypeDef *port; uint16_t pin; const char *name; } leds[] = {
    { GPIOE, GPIO_PIN_9,  "PE9  BLUE"  },
    { GPIOE, GPIO_PIN_11, "PE11 GREEN" },
    { GPIOE, GPIO_PIN_13, "PE13 YELLOW"},
    { GPIOB, GPIO_PIN_4,  "PB4  RGB_R" },
    { GPIOB, GPIO_PIN_5,  "PB5  RGB_G" },
    { GPIOB, GPIO_PIN_6,  "PB6  RGB_B" },
};
#define NUM_LEDS (sizeof(leds)/sizeof(leds[0]))

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{
    __HAL_RCC_GPIOC_CLK_ENABLE();
    printf("SD pin test (no card):\r\n");
    test_pin(GPIOC, GPIO_PIN_8,  "PC8  D0");
    test_pin(GPIOC, GPIO_PIN_9,  "PC9  D1");
    test_pin(GPIOC, GPIO_PIN_10, "PC10 D2");
    test_pin(GPIOC, GPIO_PIN_11, "PC11 D3");
    test_pin(GPIOC, GPIO_PIN_12, "PC12 CLK");
    test_pin(GPIOD, GPIO_PIN_2,  "PD2  CMD");
    test_pin(GPIOE, GPIO_PIN_3,  "PE3  CDET");
    printf("SD pin test done\r\n");
}

/* USART2: PA2=TX (AF7), PA3=RX (AF7), 115200 8N1 — v0.2 debug header */
static void USART2_Init(void)
{
    __HAL_RCC_USART2_CLK_ENABLE();
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    if (HAL_UART_Init(&huart2) != HAL_OK)
        Error_Handler();

    /* Direct register smoke test — confirms PA2 TX path before stdio init */
    const char *hw = "\r\nUART2 HW OK\r\n";
    for (const char *p = hw; *p; p++) {
        while (!(USART2->ISR & USART_ISR_TXE));
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
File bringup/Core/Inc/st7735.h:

/* vim: set ai et ts=4 sw=4: */
#ifndef __ST7735_H__
#define __ST7735_H__

#include "fonts.h"
#include <stdbool.h>

#define ST7735_MADCTL_MY  0x80
#define ST7735_MADCTL_MX  0x40
#define ST7735_MADCTL_MV  0x20
#define ST7735_MADCTL_ML  0x10
#define ST7735_MADCTL_RGB 0x00
#define ST7735_MADCTL_BGR 0x08
#define ST7735_MADCTL_MH  0x04

/*** Redefine if necessary ***/
#define ST7735_SPI_PORT hspi1
extern SPI_HandleTypeDef ST7735_SPI_PORT;

#define ST7735_RES_Pin       GPIO_PIN_1   /* PA1 = LCD_RST (v0.2) */
#define ST7735_RES_GPIO_Port GPIOA
#define ST7735_CS_Pin        GPIO_PIN_4   /* PA4 = LCD_CS */
#define ST7735_CS_GPIO_Port  GPIOA
#define ST7735_DC_Pin        GPIO_PIN_1   /* PB1 = LCD_DC (v0.2) */
#define ST7735_DC_GPIO_Port  GPIOB

// AliExpress/eBay 1.8" display, default orientation
/*
#define ST7735_IS_160X128 1
#define ST7735_WIDTH  128
#define ST7735_HEIGHT 160
#define ST7735_XSTART 0
#define ST7735_YSTART 0
#define ST7735_ROTATION (ST7735_MADCTL_MX | ST7735_MADCTL_MY)
*/

// AliExpress/eBay 1.8" display, rotate right
/*
#define ST7735_IS_160X128 1
#define ST7735_WIDTH  160
#define ST7735_HEIGHT 128
#define ST7735_XSTART 0
#define ST7735_YSTART 0
#define ST7735_ROTATION (ST7735_MADCTL_MY | ST7735_MADCTL_MV)
*/

// AliExpress/eBay 1.8" display, rotate left
/*
#define ST7735_IS_160X128 1
#define ST7735_WIDTH  160
#define ST7735_HEIGHT 128
#define ST7735_XSTART 0
#define ST7735_YSTART 0
#define ST7735_ROTATION (ST7735_MADCTL_MX | ST7735_MADCTL_MV)
*/

// AliExpress/eBay 1.8" display, upside down
/*
#define ST7735_IS_160X128 1
#define ST7735_WIDTH  128
#define ST7735_HEIGHT 160
#define ST7735_XSTART 0
#define ST7735_YSTART 0
#define ST7735_ROTATION (0)
*/

// WaveShare ST7735S-based 1.8" display, default orientation
/*
#define ST7735_IS_160X128 1
#define ST7735_WIDTH  128
#define ST7735_HEIGHT 160
#define ST7735_XSTART 2
#define ST7735_YSTART 1
#define ST7735_ROTATION (ST7735_MADCTL_MX | ST7735_MADCTL_MY | ST7735_MADCTL_RGB)
*/

// WaveShare ST7735S-based 1.8" display, rotate right
/*
#define ST7735_IS_160X128 1
#define ST7735_WIDTH  160
#define ST7735_HEIGHT 128
#define ST7735_XSTART 1
#define ST7735_YSTART 2
#define ST7735_ROTATION (ST7735_MADCTL_MY | ST7735_MADCTL_MV | ST7735_MADCTL_RGB)
*/

// WaveShare ST7735S-based 1.8" display, rotate left
/*
#define ST7735_IS_160X128 1
#define ST7735_WIDTH  160
#define ST7735_HEIGHT 128
#define ST7735_XSTART 1
#define ST7735_YSTART 2
#define ST7735_ROTATION (ST7735_MADCTL_MX | ST7735_MADCTL_MV | ST7735_MADCTL_RGB)
*/

// WaveShare ST7735S-based 1.8" display, upside down
/*
#define ST7735_IS_160X128 1
#define ST7735_WIDTH  128
#define ST7735_HEIGHT 160
#define ST7735_XSTART 2
#define ST7735_YSTART 1
#define ST7735_ROTATION (ST7735_MADCTL_RGB)
*/

// 1.44" display, default orientation
#define ST7735_IS_128X128 1
#define ST7735_WIDTH  128
#define ST7735_HEIGHT 128
#define ST7735_XSTART 2
#define ST7735_YSTART 3
#define ST7735_ROTATION (ST7735_MADCTL_MX | ST7735_MADCTL_MY | ST7735_MADCTL_BGR)

// 1.44" display, rotate right
/*
#define ST7735_IS_128X128 1
#define ST7735_WIDTH  128
#define ST7735_HEIGHT 128
#define ST7735_XSTART 3
#define ST7735_YSTART 2
#define ST7735_ROTATION (ST7735_MADCTL_MY | ST7735_MADCTL_MV | ST7735_MADCTL_BGR)
*/

// 1.44" display, rotate left
/*
#define ST7735_IS_128X128 1
#define ST7735_WIDTH  128
#define ST7735_HEIGHT 128
#define ST7735_XSTART 1
#define ST7735_YSTART 2
#define ST7735_ROTATION (ST7735_MADCTL_MX | ST7735_MADCTL_MV | ST7735_MADCTL_BGR)
*/

// 1.44" display, upside down
/*
#define ST7735_IS_128X128 1
#define ST7735_WIDTH  128
#define ST7735_HEIGHT 128
#define ST7735_XSTART 2
#define ST7735_YSTART 1
#define ST7735_ROTATION (ST7735_MADCTL_BGR)
*/

// mini 160x80 display (it's unlikely you want the default orientation)
/*
#define ST7735_IS_160X80 1
#define ST7735_XSTART 26
#define ST7735_YSTART 1
#define ST7735_WIDTH  80
#define ST7735_HEIGHT 160 
#define ST7735_ROTATION (ST7735_MADCTL_MX | ST7735_MADCTL_MY | ST7735_MADCTL_BGR)
*/

// mini 160x80, rotate left
/*
#define ST7735_IS_160X80 1
#define ST7735_XSTART 1
#define ST7735_YSTART 26
#define ST7735_WIDTH  160
#define ST7735_HEIGHT 80
#define ST7735_ROTATION (ST7735_MADCTL_MX | ST7735_MADCTL_MV | ST7735_MADCTL_BGR)
*/

// mini 160x80, rotate right 
/*
#define ST7735_IS_160X80 1
#define ST7735_XSTART 1
#define ST7735_YSTART 26
#define ST7735_WIDTH  160
#define ST7735_HEIGHT 80
#define ST7735_ROTATION (ST7735_MADCTL_MY | ST7735_MADCTL_MV | ST7735_MADCTL_BGR)
*/

/****************************/

#define ST7735_NOP     0x00
#define ST7735_SWRESET 0x01
#define ST7735_RDDID   0x04
#define ST7735_RDDST   0x09

#define ST7735_SLPIN   0x10
#define ST7735_SLPOUT  0x11
#define ST7735_PTLON   0x12
#define ST7735_NORON   0x13

#define ST7735_INVOFF  0x20
#define ST7735_INVON   0x21
#define ST7735_GAMSET  0x26
#define ST7735_DISPOFF 0x28
#define ST7735_DISPON  0x29
#define ST7735_CASET   0x2A
#define ST7735_RASET   0x2B
#define ST7735_RAMWR   0x2C
#define ST7735_RAMRD   0x2E

#define ST7735_PTLAR   0x30
#define ST7735_COLMOD  0x3A
#define ST7735_MADCTL  0x36

#define ST7735_FRMCTR1 0xB1
#define ST7735_FRMCTR2 0xB2
#define ST7735_FRMCTR3 0xB3
#define ST7735_INVCTR  0xB4
#define ST7735_DISSET5 0xB6

#define ST7735_PWCTR1  0xC0
#define ST7735_PWCTR2  0xC1
#define ST7735_PWCTR3  0xC2
#define ST7735_PWCTR4  0xC3
#define ST7735_PWCTR5  0xC4
#define ST7735_VMCTR1  0xC5

#define ST7735_RDID1   0xDA
#define ST7735_RDID2   0xDB
#define ST7735_RDID3   0xDC
#define ST7735_RDID4   0xDD

#define ST7735_PWCTR6  0xFC

#define ST7735_GMCTRP1 0xE0
#define ST7735_GMCTRN1 0xE1

// Color definitions
#define	ST7735_BLACK   0x0000
#define	ST7735_BLUE    0x001F
#define	ST7735_RED     0xF800
#define	ST7735_GREEN   0x07E0
#define ST7735_CYAN    0x07FF
#define ST7735_MAGENTA 0xF81F
#define ST7735_YELLOW  0xFFE0
#define ST7735_WHITE   0xFFFF
#define ST7735_COLOR565(r, g, b) (((r & 0xF8) << 8) | ((g & 0xFC) << 3) | ((b & 0xF8) >> 3))

typedef enum {
	GAMMA_10 = 0x01,
	GAMMA_25 = 0x02,
	GAMMA_22 = 0x04,
	GAMMA_18 = 0x08
} GammaDef;

#ifdef __cplusplus
extern "C" {
#endif

// call before initializing any SPI devices
void ST7735_Unselect();

void ST7735_Init(void);
void ST7735_DrawPixel(uint16_t x, uint16_t y, uint16_t color);
void ST7735_WriteString(uint16_t x, uint16_t y, const char* str, FontDef font, uint16_t color, uint16_t bgcolor);
void ST7735_FillRectangle(uint16_t x, uint16_t y, uint16_t w, uint16_t h, uint16_t color);
void ST7735_FillRectangleFast(uint16_t x, uint16_t y, uint16_t w, uint16_t h, uint16_t color);
void ST7735_FillScreen(uint16_t color);
void ST7735_FillScreenFast(uint16_t color);
void ST7735_DrawImage(uint16_t x, uint16_t y, uint16_t w, uint16_t h, const uint16_t* data);
void ST7735_InvertColors(bool invert);
void ST7735_SetGamma(GammaDef gamma);

#ifdef __cplusplus
}
#endif

#endif // __ST7735_H__

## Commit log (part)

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2026-04-24 Initial skeleton for STM32F723 passthrough demo
2026-04-24 Pickup latest ( match gerbers/USB-passthrough.zip)
2026-04-24 Pickup files missed in initial skeleton
2026-04-24 Pickup deletion
2026-05-08 Cleanup for v0.2 PBC
2026-05-09 Unrouted v0.2 PCB
2026-05-09 Resolve DRC errors on unrouted PCB
2026-05-09 Update gitignore
2026-05-09 Add initial v0.2 PCB layout, unrouted
2026-05-10 Update schematic
    Change JP2 to Open to reflect v0.2
2026-05-10 Generate clean unrouted PCB
    1. place components
    2. manually route USB differential signals
    3. manually route Power Supply
    4. connect 3V3 and GND to energize power planes
2026-05-10 Capture routed PCB
    1. results of FreeRouting
    2. manually tweak routing
    3. route/connect 3V3 and GND
2026-05-10 Update LED 2 footprint
2026-05-10 Tweak PCB
    1. Import LED2 footprint update
    2. Move TP8
    3. Adjust silkscreen
2026-05-10 Tweak PCB
    1. adjust some signals
    2. Increase the size of the +5V trace to the USBA connector
2026-05-11 Update PCB
    1. Move SD socket to bottom of board (to reduce size of PCB)
    2. Reduce size of PCB
    3. reroute traces
2026-05-11 Tweak PCD and slikscreen
    1. Reroute traces to clear Xtal footprint
    2. Label pins on SWD header (move resistors)
2026-05-11 Realign pin 1 of components, up and left
2026-05-11 Silkscreen tweaks
2026-05-12 Rework ID jumper labeling
2026-05-12 Reannotate based on position on PCB
2026-05-12 Fix ID jumper references
2026-05-12 Add labels to Boot0 and Reset buttons
2026-05-12 Reroute SWDIO trace that was awkward
2026-05-12 Clean up traces
2026-05-21 Clarify hardware version details in README
    Updated hardware version descriptions for clarity.
2026-05-21 Enhance README with project learning objectives
    Expanded project description to include learning goals and hardware design.
2026-05-21 Add U1 pi 1 mark
2026-05-22 Change incorrect metric footprints to imperial
2026-05-29 Add .gitignore
2026-05-29 Cleanup build
2026-05-29 Remove ignored file
2026-05-31 Clean up SWD connector
    Make pins conform to Nucleo connector
    Rename SoC to R signals
2026-06-02 Cleanup labeling
2026-06-19 Fix problem with bypass caps on VDDA and VDDPHYHS
2026-06-26 fix capacitor footprints
